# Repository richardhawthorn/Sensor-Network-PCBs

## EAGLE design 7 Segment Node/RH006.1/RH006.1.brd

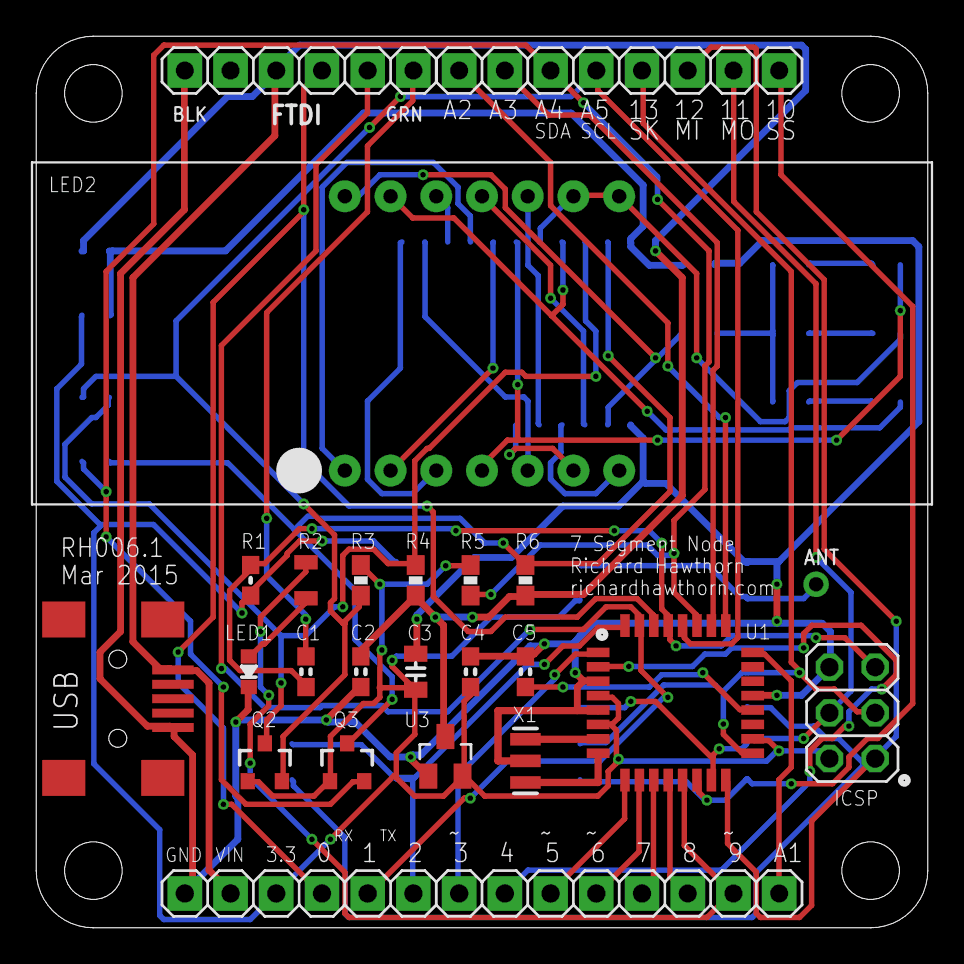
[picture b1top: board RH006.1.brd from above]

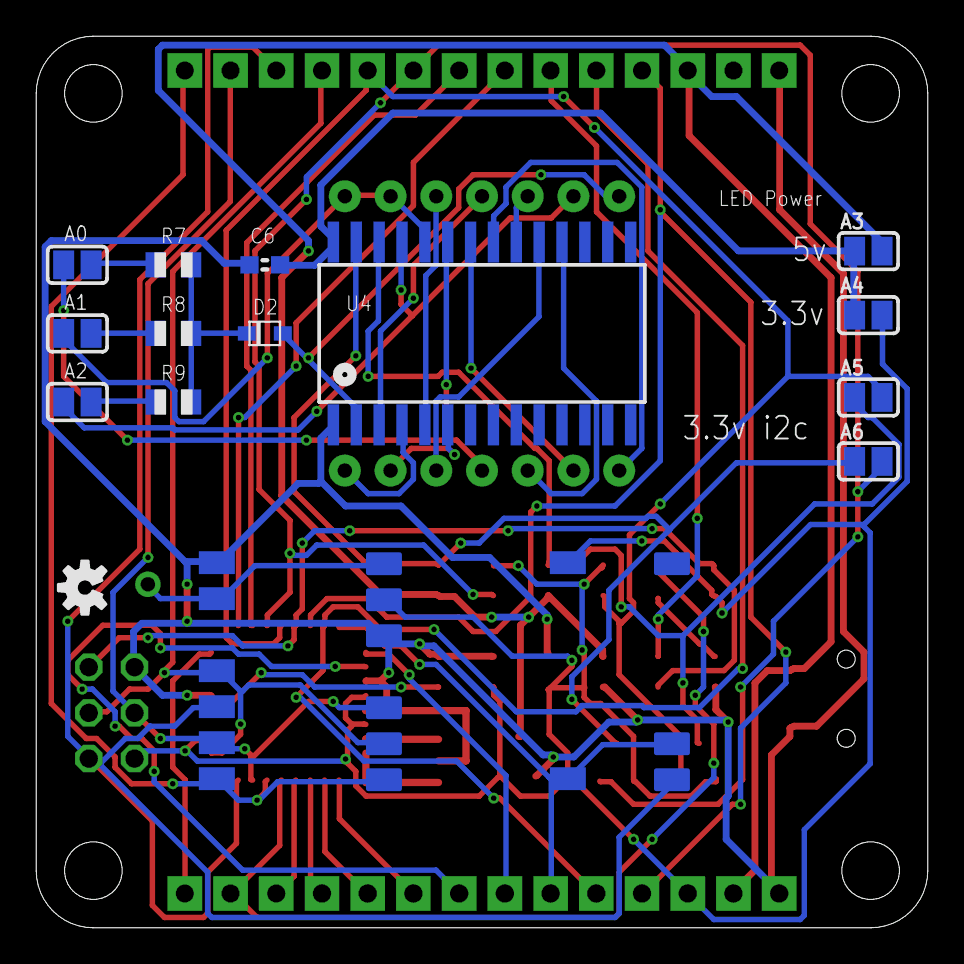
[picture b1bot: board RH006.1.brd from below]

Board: 2 copper layers, 49.5 x 49.5 mm, 40 parts (16 on the bottom side), 49 nets.

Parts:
A0, A1, A2: SOLDERJUMPER_REFLOW_NOPASTE
A3: 5V; SOLDERJUMPER_REFLOW_NOPASTE
A4: 3.3V; SOLDERJUMPER_REFLOW_NOPASTE
A5: SCL; SOLDERJUMPER_REFLOW_NOPASTE
A6: SDA; SOLDERJUMPER_REFLOW_NOPASTE
C1, C4, C5, C6: 0.1; 0603-CAP
C2: 1u; 0603-CAP
C3: 10u; 0805-CAP
CN1: USB; USB-MINIB
CN4: FTDI; 1X06
D2: 1N4148; SOD-323F
ICSP1: ICSP; 2X03
JP3: 1X14
JP5: 1X08
LED1: LED0603; 0603-LED
LED2: SEGMENT-BL-Q56C43
Q2, Q3: BSS138; SOT23-3
R1: 10k; 0603-RES
R2: 1k5; 0805
R3, R4, R5, R6: 10K; 0603-RES
R7, R8, R9: 47K; R0805
RF1: RFM12B; RFM12B-MINPADS
RF2: RFM69; RFM69W-MINPADS
U1: ATMega-328; TQFP32-08
U3: MCP1703CB; SOT23
U4: SOP28_300MIL
U$1: RFM12B_ANTENNA; RFM12B-ANTENNA
U$3: OSHW-LOGO-S
X1: 16 MHz; RESONATOR-SMD

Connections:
3.3V: A4.2, C3.1, C4.1, ICSP1.2, JP3.12, Q2.1, Q3.1, R1.1, R3.1, R5.1, RF1.VDD, RF2.VDD, U1.4, U1.6, U1.18, U3.2
A1: JP3.1, U1.24
A2: JP5.1, U1.25
A3: JP5.2, U1.26
A4_SDA: A6.2, JP5.3, Q3.2, R5.2, U1.27
A5_SCL: A5.2, JP5.4, Q2.2, R3.2, U1.28
ADD0: A0.2, LED2.P$4, U4.P$23
ADD1: A1.2, LED2.P$8, LED2.P$9, U4.P$24
ADD2: A2.2, LED2.P$13, U4.P$25
AREF: C5.1, U1.20
COM: D2.A, LED2.P$14, U4.P$2
D0_RX: CN4.4, JP3.11, U1.30
D1_TX: CN4.5, JP3.10, U1.31
D2: JP3.9, RF1.IRQ, RF2.DIO0, U1.32
D3: JP3.8, U1.1
D4: JP3.7, U1.2
D5: JP3.6, U1.9
D6: JP3.5, U1.10
D7: JP3.4, U1.11
D8: JP3.3, U1.12
D9: JP3.2, R2.2, U1.13
D10_SS: JP5.8, RF1.SEL, RF2.NSS, U1.14
D11_MOSI: ICSP1.4, JP5.7, RF1.SDI, RF2.MOSI, U1.15
D12_MISO: ICSP1.1, JP5.6, RF1.SDO, RF2.MISO, U1.16
D13_SCK: ICSP1.3, JP5.5, RF1.SCK, RF2.SCK, U1.17
GND: C2.2, C3.2, C4.2, C5.2, C6.2, CN1.GND, CN4.1, ICSP1.6, JP3.14, LED1.MINUS, RF1.GND, RF2.GND, U1.3, U1.5, U1.21, U3.1, U4.P$1, X1.2
unnamed: U1.7, X1.1
unnamed: LED1.PLUS, R2.1
unnamed: RF1.ANT, RF2.ANA, U$1.P$1
unnamed: A0.1, R7.2
unnamed: LED2.P$11, U4.P$3
unnamed: LED2.P$7, U4.P$4
unnamed: LED2.P$10, U4.P$5
unnamed: LED2.P$6, U4.P$6
unnamed: LED2.P$2, U4.P$22
unnamed: LED2.P$1, U4.P$21
unnamed: LED2.P$12, U4.P$20
unnamed: LED2.P$5, U4.P$19
unnamed: LED2.P$3, U4.P$18
unnamed: D2.C, R7.1, R8.1, R9.1
unnamed: A2.1, R9.2
unnamed: A1.1, R8.2
unnamed: C1.2, CN4.6
unnamed: U1.8, X1.3
RST: C1.1, ICSP1.5, R1.2, U1.29
SCL: A5.1, Q2.3, R4.2, U4.P$26
SDA: A6.1, Q3.3, R6.2, U4.P$27
VBUS: A3.2, C2.1, CN1.VBUS, CN4.3, JP3.13, R4.1, R6.1, U3.3
VLED: A3.1, A4.1, C6.1, U4.P$28

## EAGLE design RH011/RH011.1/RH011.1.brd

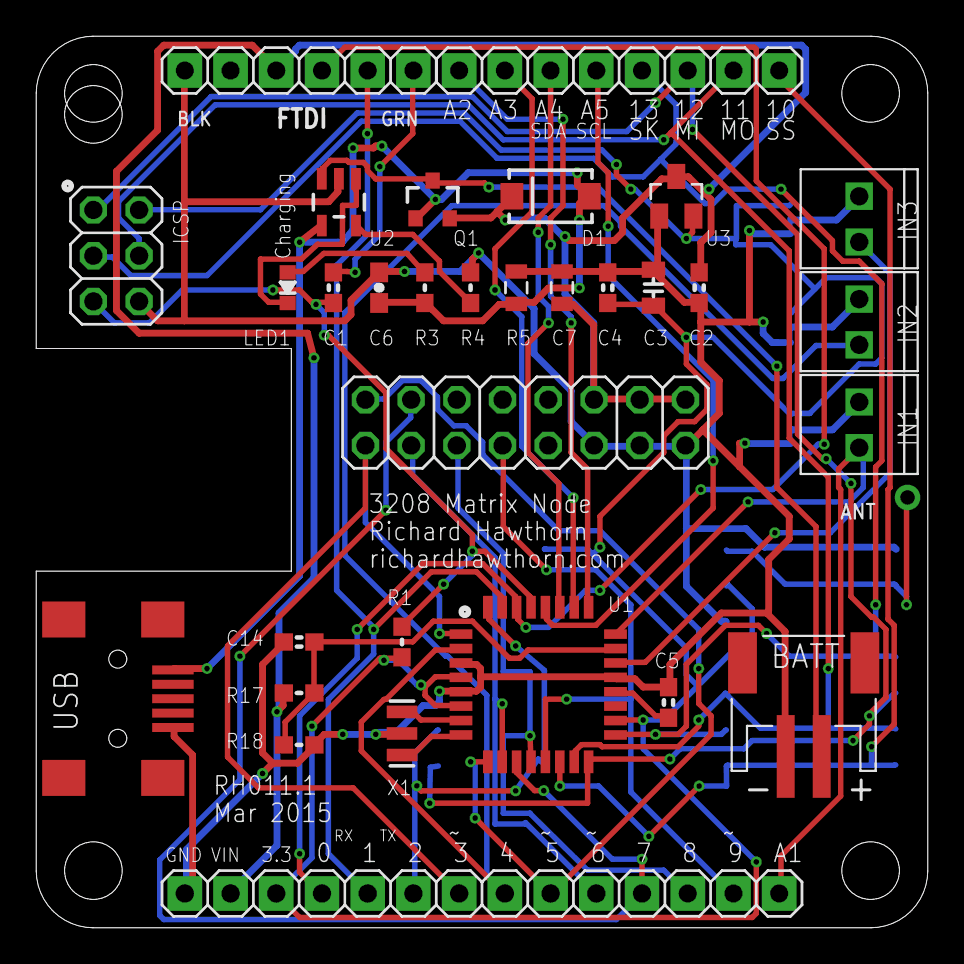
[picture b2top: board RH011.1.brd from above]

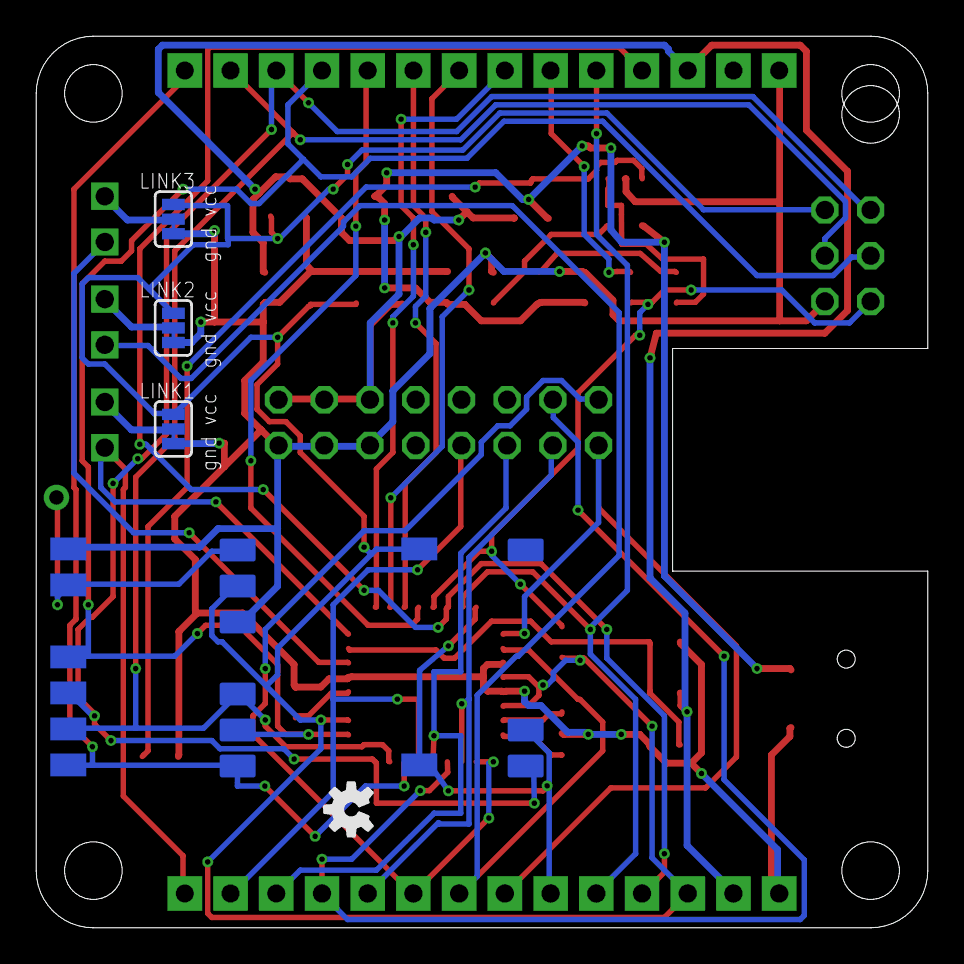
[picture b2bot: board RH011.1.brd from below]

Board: 2 copper layers, 49.5 x 49.5 mm, 38 parts (6 on the bottom side), 38 nets.

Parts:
C1, C4, C5, C14: 0.1; 0603-CAP
C2: 1u; 0603-CAP
C3: 10u; 0805-CAP
C6: 4u7; 0603-CAP
C7: 1 uF; 0805
CN1: USB; USB-MINIB
CN3: BATT; JST-PH-2-SMT-RA
CN4: FTDI; 1X06
D1: SCHOTTKY; SMA-DIODE
ICSP1: ICSP; 2X03
IN1, IN2, IN3: M022.54MM_SCREWTERM; 1X02_2.54_SCREWTERM
JP1: 2X08
JP3: 1X14
JP5: 1X08
LED1: LED0603; 0603-LED
LINK1, LINK2, LINK3: JUMPER-PAD-3-2OF3_NC_BY_TRACE; PAD-JUMPER-3-2OF3_NC_BY_TRACE_YES_SILK_FULL_BOX
Q1: MOSFET; SOT23-3
R1: 10k; 0603-RES
R3: 1k5; 0603-RES
R4: 2K; 0603-RES
R5: 100 K; 0805
R17, R18: 470k; 0603-RES
RF1: RFM12B; RFM12B-MINPADS
RF2: RFM69; RFM69W-MINPADS
U1: ATMega-328; TQFP32-08
U2: MCP73831; SOT23-5
U3: MCP1703CB; SOT23
U$1: RFM12B_ANTENNA; RFM12B-ANTENNA
U$3: OSHW-LOGO-S
X1: 16 MHz; RESONATOR-SMD

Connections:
3.3V: C3.1, C4.1, ICSP1.2, JP3.12, LINK1.1, LINK2.1, LINK3.1, R1.1, RF1.VDD, RF2.VDD, U1.4, U1.6, U1.18, U3.2
A0: C14.1, R17.1, R18.2, U1.23
A1: IN1.P1, JP3.1, U1.24
A2: JP5.1, U1.25
A3: JP5.2, U1.26
A4_SDA: JP5.3, U1.27
A5_SCL: JP5.4, U1.28
A7: IN3.P1, U1.22
AREF: C5.1, U1.20
D0_RX: CN4.4, JP3.11, U1.30
D1_TX: CN4.5, JP3.10, U1.31
D2: JP3.9, RF1.IRQ, RF2.DIO0, U1.32
D3: JP1.1, JP3.8, U1.1
D4: IN2.P1, JP3.7, U1.2
D5: JP1.2, JP3.6, U1.9
D6: JP1.3, JP3.5, U1.10
D7: JP1.4, JP3.4, U1.11
D8: JP1.5, JP3.3, U1.12
D9: JP1.7, JP3.2, U1.13
D10_SS: JP5.8, RF1.SEL, RF2.NSS, U1.14
D11_MOSI: ICSP1.4, JP5.7, RF1.SDI, RF2.MOSI, U1.15
D12_MISO: ICSP1.1, JP5.6, RF1.SDO, RF2.MISO, U1.16
D13_SCK: ICSP1.3, JP5.5, RF1.SCK, RF2.SCK, U1.17
GND: C2.2, C3.2, C4.2, C5.2, C6.2, C7.2, C14.2, CN1.GND, CN3.2, CN4.1, ICSP1.6, JP1.11, JP1.13, JP1.15, JP3.14, LINK1.3, LINK2.3, LINK3.3, R4.1, R5.1, R18.1, RF1.GND, RF2.GND, U1.3, U1.5, U1.21, U2.2, U3.1, X1.2
unnamed: U1.7, X1.1
unnamed: RF1.ANT, RF2.ANA, U$1.P$1
unnamed: LED1.PLUS, R3.2
unnamed: IN1.P2, LINK1.2
unnamed: IN2.P2, LINK2.2
unnamed: IN3.P2, LINK3.2
unnamed: C1.2, CN4.6
unnamed: U1.8, X1.3
PROG: R4.2, U2.5
PWR: C2.1, C7.1, CN4.3, D1.C, JP1.12, JP1.14, JP1.16, JP3.13, Q1.2, R17.2, U3.3
RST: C1.1, ICSP1.5, R1.2, U1.29
STAT: LED1.MINUS, U2.1
VBAT: CN3.1, Q1.3, U2.3
VBUS: C6.1, CN1.VBUS, D1.A, Q1.1, R3.1, R5.2, U2.4

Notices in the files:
parts and their libraries:
SparkFun-Aesthetics: Licensing: CC v3.0 Share-Alike You are welcome to use this library for commercial purposes.
SparkFun-Connectors: Licensing: Creative Commons ShareAlike 4.0 International - https://creativecommons.org/licenses/by-sa/4.0
